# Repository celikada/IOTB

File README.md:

# IOTB
### Internet of Things Device
#### Version 3.0: 2021-1-17 [Wiki](https://github.com/celikada/IOTB/wiki)

#### Get expedited support or integration consultation for IOTB [from IOTECH](http://iotech.com.tr/)

---

### OVERVIEW:
IOTB is an internet of things edge device implementation. The hardware has digital inputs and outputs and offers connectivity for analog sensors and extensions.
It has open source firmware and upload ready various tcp/ip connection options according to needs.

**It is a platform**

IOTB is a platform that users can create and upload a firmware which they needed. 

**Main features:**
1. 100Mb Ethernet.
2. TTL Serial connection.
3. 8 Digital Inputs.
4. 8 Digital Outputs.
5. 5V-26V operational power range.
6. Opto isolation for IO.
7. 2 line (4+4) Isolated input voltage. 
8. Isolaated Output voltage.
9. Current protection for outputs.
10. Voltage progection for outputs.

STM32 architectute. Modbus and MQTT ready software.

### Changelog is located [here.](https://github.com/celikada/IOTB/wiki/Changelog)

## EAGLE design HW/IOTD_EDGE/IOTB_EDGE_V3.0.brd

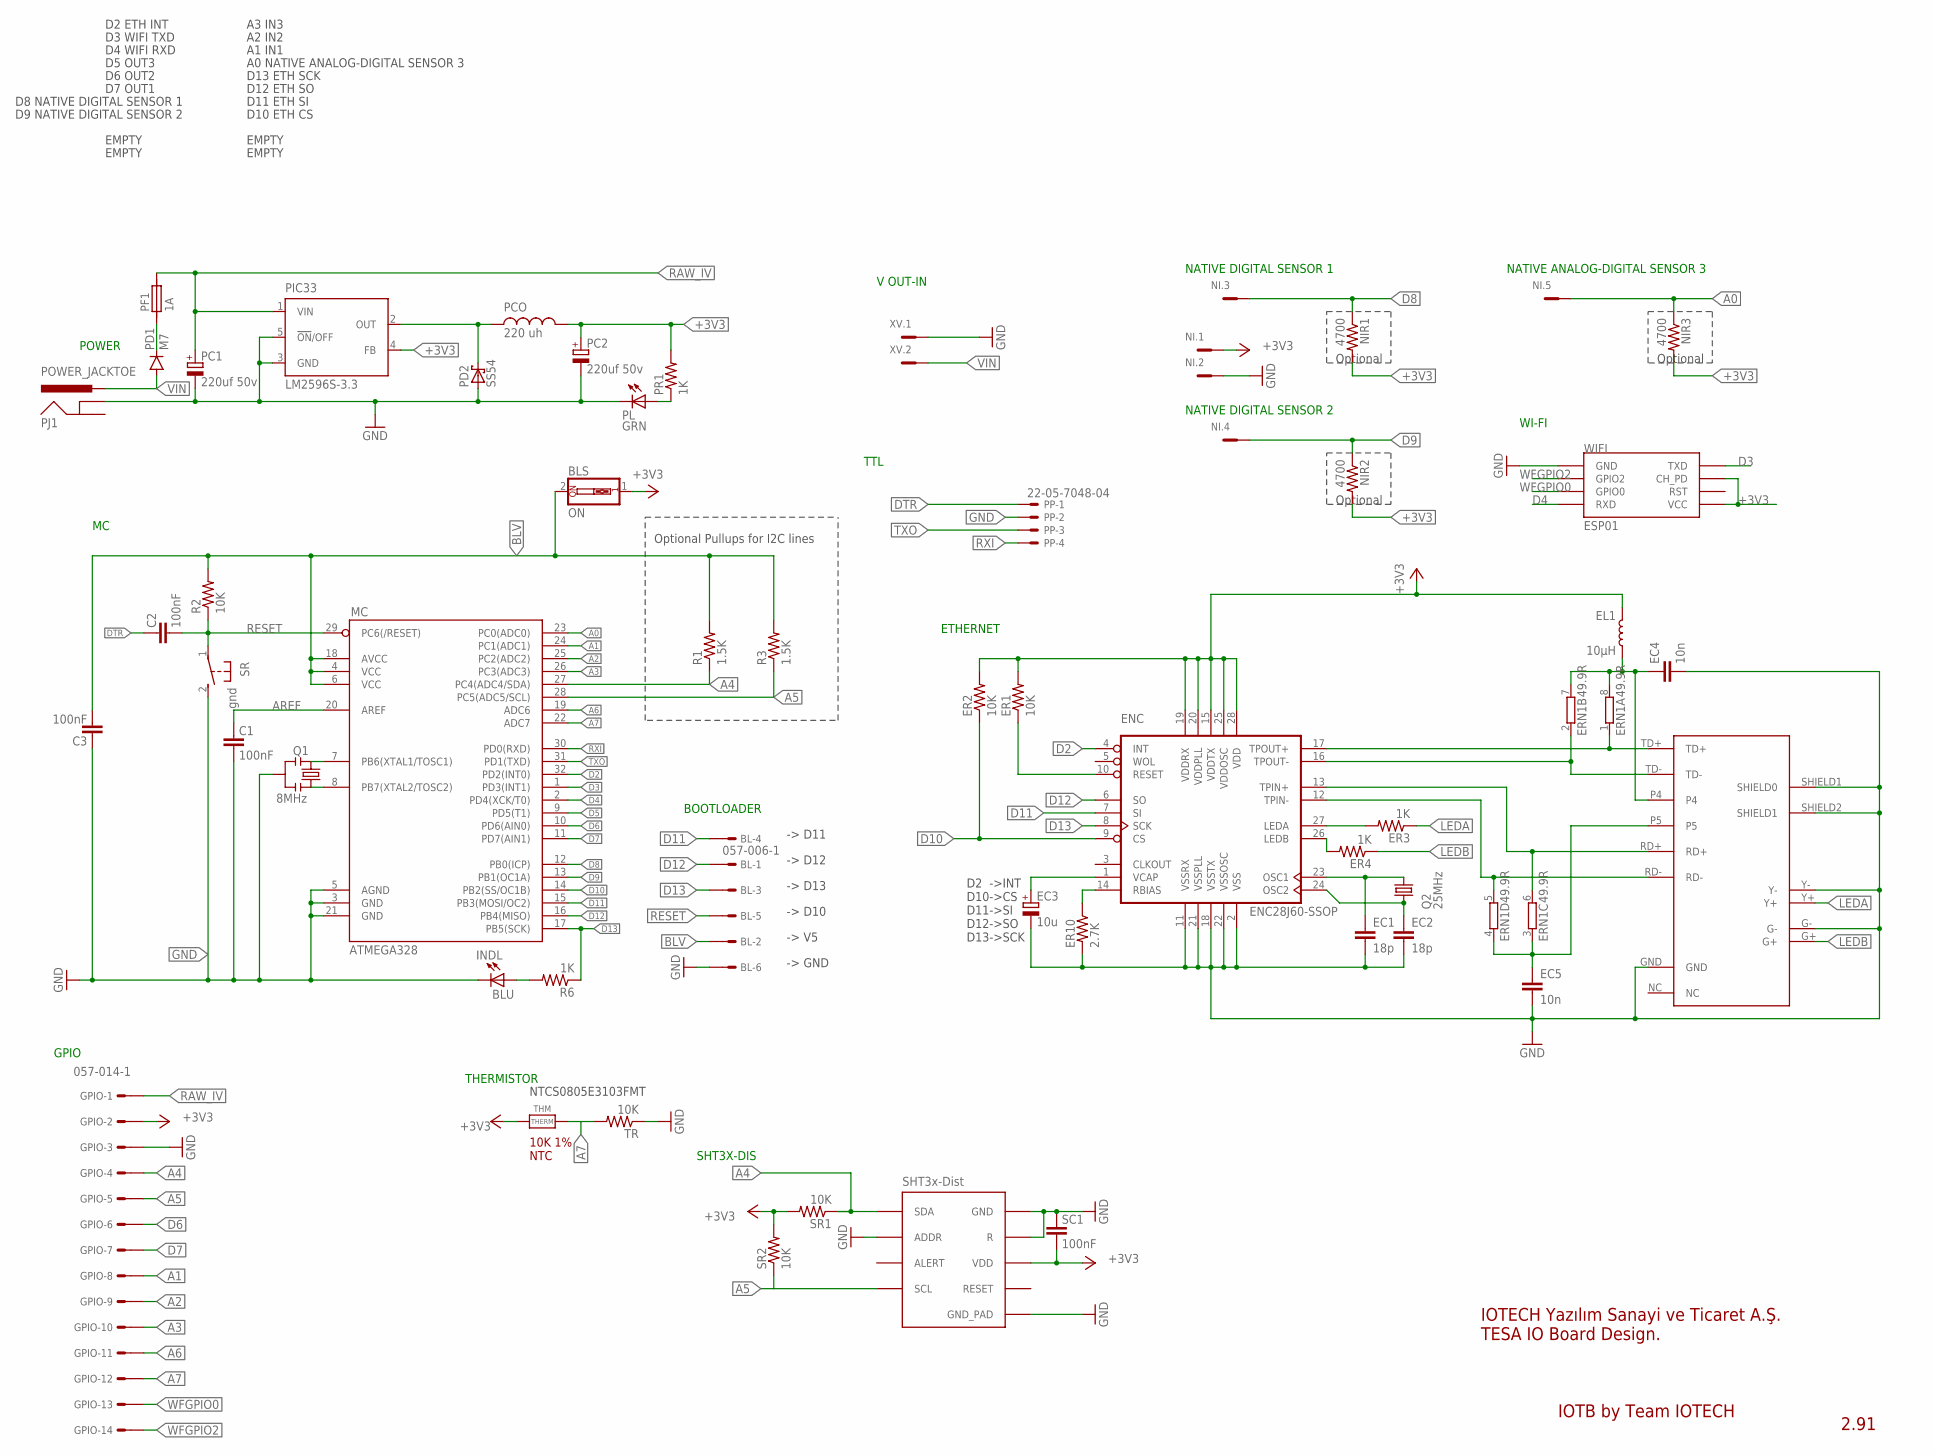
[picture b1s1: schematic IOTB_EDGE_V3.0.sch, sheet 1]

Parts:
BL: 057-006-1
BLS: ON; EDG-01
C1, C2, C3: 100nF; 0805
EC1, EC2: 18p; 0805
EC3: 10u; CT3216
EC4, EC5: 10n; 0805
EL1: 10µH; 0805
ENC: ENC28J60-SSOP; SSOP28
ER1, ER2: 10K; 0805
ER3, ER4: 1K; 0805
ER10: 2.7K; 0805
ERN1: 49.9R; 0603-ARV
ETHSOC: HR911105A; RJ45
GPIO: 057-014-1
INDL: BLU; CHIP-LED0805
MC: ATMEGA328; TQFP32-08
NI: MC5
NIR1, NIR2, NIR3: 4700; 0805
PC1, PC2: 220uf 50v; 140CLH-1010
PCO: 220 uh; MSS1260
PD1: M7; SMA-DIODE
PD2: SS54; SMB
PF1: 1A; 1820
PIC33: LM2596S-3.3; TO263-5
PJ1: POWER_JACKTOE; POWER_JACK_SMD_OVERPASTE_TOE
PL: GRN; CHIP-LED0805
PP: 22-05-7048-04; 7395-04
PR1: 1K; 0805
Q1: 8MHz; RESONATOR-SMD-1:1
Q2: 25MHz; 5.0X3.2_2
R1, R3: 1.5K; 0805
R2: 10K; 0805
R6: 1K; 0805
SC1: 100nF; 0805
SHT: SHT3X
SR: gnd; B3F-31XX
SR1, SR2: 10K; 0805
THM: THERM; MICROBUILDER_0805_NOTHERMALS
TR: 10K; 0805
WIFI: ESP01
XV: MC2

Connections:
+3V3: BLS.1, EL1.1, ENC.15 (VDDTX), ENC.19 (VDDRX), ENC.20 (VDDPLL), ENC.25 (VDDOSC), ENC.28 (VDD), ER1.2, ER2.2, GPIO.2, NI.1, NIR1.2, NIR2.2, NIR3.2, PC2.+, PCO.P$1, PIC33.4 (FB), PR1.2, SC1.1, SHT.VDD, SR1.2, SR2.2, THM.1, WIFI.CH_PD, WIFI.VCC; also elsewhere on the board
A0: MC.23 (PC0(ADC0)), NI.5, NIR3.1
A1: GPIO.8, MC.24 (PC1(ADC1))
A2: GPIO.9, MC.25 (PC2(ADC2))
A3: GPIO.10, MC.26 (PC3(ADC3))
A4: GPIO.4, MC.27 (PC4(ADC4/SDA)), R1.1, SHT.SDA, SR1.1; also elsewhere on the board
A5: GPIO.5, MC.28 (PC5(ADC5/SCL)), R3.1, SHT.SCL, SR2.1; also elsewhere on the board
A6: GPIO.11, MC.19 (ADC6)
A7: GPIO.12, MC.22 (ADC7), THM.2, TR.2
AREF: C1.2, MC.20 (AREF)
BLV: BL.2, BLS.2, C3.1, MC.4 (VCC), MC.6 (VCC), MC.18 (AVCC), R1.2, R2.2, R3.2
D2: ENC.4 (INT), MC.32 (PD2(INT0))
D3: MC.1 (PD3(INT1)), WIFI.TX (TXD)
D4: MC.2 (PD4(XCK/T0)), WIFI.RX (RXD)
D5: MC.9 (PD5(T1)); also elsewhere on the board
D6: GPIO.6, MC.10 (PD6(AIN0))
D7: GPIO.7, MC.11 (PD7(AIN1))
D8: MC.12 (PB0(ICP)), NI.3, NIR1.1
D9: MC.13 (PB1(OC1A)), NI.4, NIR2.1
D10: ENC.9 (CS), ER2.1, MC.14 (PB2(SS/OC1B))
D11: BL.4, ENC.7 (SI), MC.15 (PB3(MOSI/OC2))
D12: BL.1, ENC.6 (SO), MC.16 (PB4(MISO))
D13: BL.3, ENC.8 (SCK), MC.17 (PB5(SCK)), R6.1
DTR: C2.2, PP.1
EP4: EC4.1, EL1.2, ERN1.7 (2), ERN1.8 (2), ETHSOC.P4
EP5: EC5.1, ERN1.3 (1), ERN1.4 (1), ETHSOC.P5
GND: BL.6, C1.1, C3.2, EC1.2, EC2.2, EC3.-, EC4.2, EC5.2, ENC.2 (VSS), ENC.11 (VSSRX), ENC.18 (VSSTX), ENC.21 (VSSPLL), ENC.22 (VSSOSC), ER10.2, ETHSOC.G-, ETHSOC.GND, ETHSOC.SHIELD1 (SHIELD0), ETHSOC.SHIELD2 (SHIELD1), ETHSOC.Y-, GPIO.3, INDL.C, MC.3 (GND), MC.5 (AGND), MC.21 (GND), NI.2, PC1.-, PC2.-, PD2.A, PIC33.3 (GND), PIC33.5 (!ON!/OFF), PJ1.GND (GNDBREAK), PL.C, PP.2, Q1.2, SC1.2, SHT.ADDR, SHT.GND, SHT.GND_PAD, SHT.R, SR.2 (S), TR.1, WIFI.GND, XV.1; also elsewhere on the board
LEDA: ER3.1, ETHSOC.Y+
LEDB: ER4.1, ETHSOC.G+
unnamed: PD1.C, PF1.1
unnamed: INDL.A, R6.2
unnamed: ENC.27 (LEDA), ER3.2
unnamed: MC.8 (PB7(XTAL2/TOSC2)), Q1.3
unnamed: PL.A, PR1.1
unnamed: EC3.+, ENC.1 (VCAP)
unnamed: ENC.26 (LEDB), ER4.2
unnamed: MC.7 (PB6(XTAL1/TOSC1)), Q1.1
unnamed: PCO.P$2, PD2.C, PIC33.2 (OUT)
unnamed: ENC.10 (RESET), ER1.1
unnamed: ENC.14 (RBIAS), ER10.1
unnamed: EC2.1, ENC.24 (OSC2), Q2.1
unnamed: EC1.1, ENC.23 (OSC1), Q2.2
RAW_IV: GPIO.1, PC1.+, PF1.2, PIC33.1 (VIN)
RD+: ENC.13 (TPIN+), ERN1.6 (2), ETHSOC.RD+
RD-: ENC.12 (TPIN-), ERN1.5 (2), ETHSOC.RD-
RESET: BL.5, C2.1, MC.29 (PC6(/RESET)), R2.1, SR.1
RXI: MC.30 (PD0(RXD)), PP.4
TD+: ENC.17 (TPOUT+), ERN1.1, ETHSOC.TD+
TD-: ENC.16 (TPOUT-), ERN1.2 (1), ETHSOC.TD-
TXO: MC.31 (PD1(TXD)), PP.3
VIN: PD1.A, PJ1.VIN0 (PWR), XV.2
WFGPIO0: GPIO.13, WIFI.GPIO0
WFGPIO2: GPIO.14, WIFI.GPIO2

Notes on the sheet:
POWER
NATIVE DIGITAL SENSOR 1
NATIVE DIGITAL SENSOR 2
WI-FI
NATIVE ANALOG-DIGITAL SENSOR 3
IOTB by Team IOTECH
2.91
ETHERNET
D2 ->INT D10->CS D11->SI D12->SO D13->SCK
TTL
IOTECH Yazılım Sanayi ve Ticaret A.Ş. TESA IO Board Design.
Optional Pullups for I2C lines
D2 ETH INT
D8 NATIVE DIGITAL SENSOR 1
D9 NATIVE DIGITAL SENSOR 2
EMPTY
A3 IN3
A2 IN2
A1 IN1
A0 NATIVE ANALOG-DIGITAL SENSOR 3
D13 ETH SCK
D12 ETH SO
D11 ETH SI
D10 ETH CS
D4 WIFI RXD
D3 WIFI TXD
D7 OUT1
D6 OUT2
D5 OUT3
BOOTLOADER
-> D11
-> D12
-> D13
-> D10
-> V5
-> GND
Optional
V OUT-IN
GPIO
NTCS0805E3103FMT

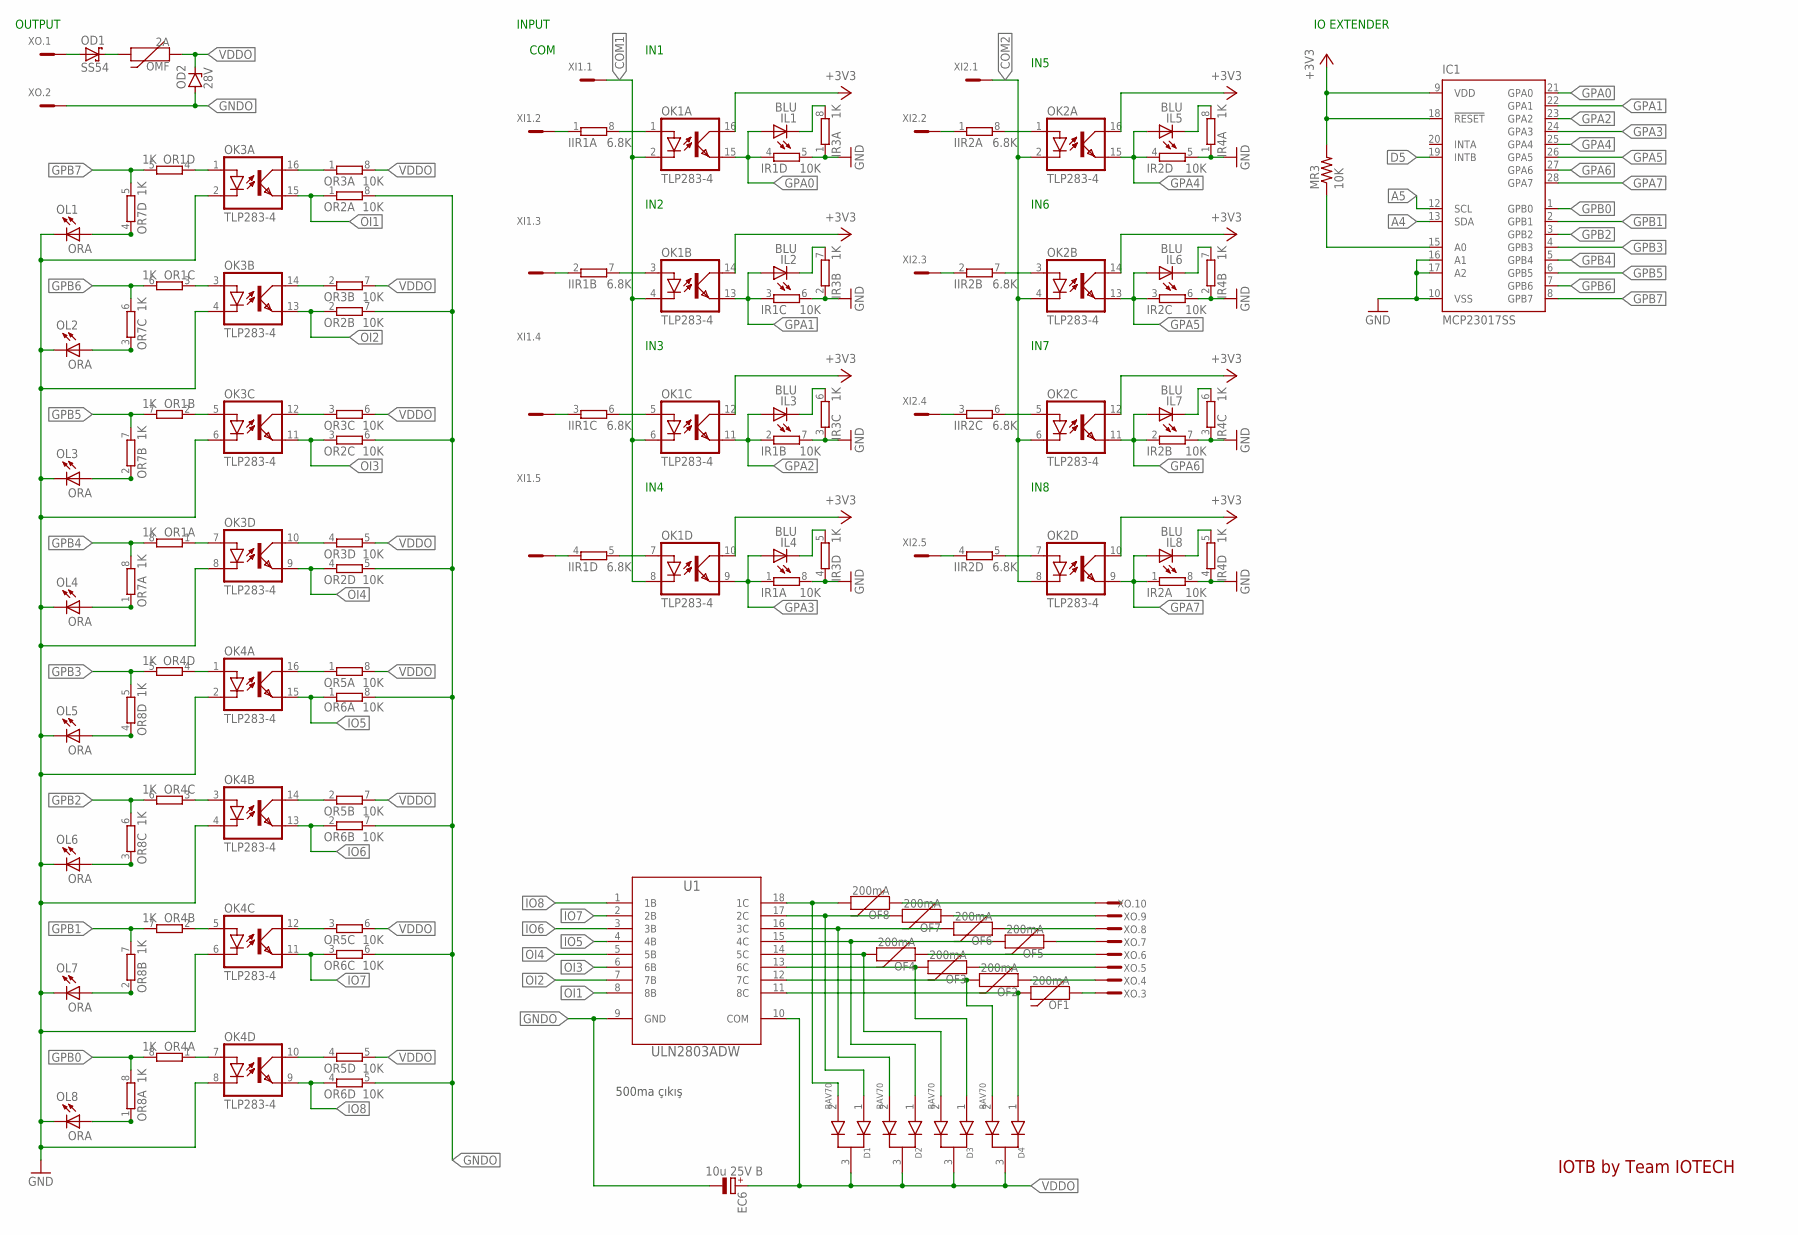
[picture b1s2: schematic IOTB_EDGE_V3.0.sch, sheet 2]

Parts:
D1, D2, D3, D4: BAV70; SOT-23-3
EC6: 10u 25V B; SMC_B
IC1: MCP23017SS; SSOP28
IIR1, IIR2: 6.8K; 0603-ARV
IL1, IL2, IL3, IL4, IL5, IL6, IL7, IL8: BLU; CHIP-LED0805
IR1, IR2: 10K; 0603-ARV
IR3, IR4: 1K; 0603-ARV
MR3: 10K; 0805
OD1: SS54; SMB
OD2: 28V; SMB
OF1, OF2, OF3, OF4, OF5, OF6, OF7, OF8: 200mA; 1206
OK1, OK2, OK3, OK4: TLP283-4; MINI-FLAT-16
OL1, OL2, OL3, OL4, OL5, OL6, OL7, OL8: ORA; CHIP-LED0805
OMF: 2A; 1206
OR1, OR4, OR7, OR8: 1K; 0603-ARV
OR2, OR3, OR5, OR6: 10K; 0603-ARV
U1: ULN2803ADW; SOIC127P1030X265-18N
XI1, XI2: MC5
XO: MC10

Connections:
+3V3: IC1.9 (VDD), IC1.18 (!RESET), MR3.2, OK1.10 (COL), OK1.12 (COL), OK1.14 (COL), OK1.16 (COL), OK2.10 (COL), OK2.12 (COL), OK2.14 (COL), OK2.16 (COL); also elsewhere on the board
A4: IC1.13 (SDA); also elsewhere on the board
A5: IC1.12 (SCL); also elsewhere on the board
COM1: OK1.2 (C), OK1.4 (C), OK1.6 (C), OK1.8 (C), XI1.1
COM2: OK2.2 (C), OK2.4 (C), OK2.6 (C), OK2.8 (C), XI2.1
D5: IC1.19 (INTB); also elsewhere on the board
GND: IC1.10 (VSS), IC1.16 (A1), IC1.17 (A2), IR1.5 (2), IR1.6 (2), IR1.7 (2), IR1.8 (2), IR2.5 (2), IR2.6 (2), IR2.7 (2), IR2.8 (2), IR3.1, IR3.2 (1), IR3.3 (1), IR3.4 (1), IR4.1, IR4.2 (1), IR4.3 (1), IR4.4 (1), OK3.2 (C), OK3.4 (C), OK3.6 (C), OK3.8 (C), OK4.2 (C), OK4.4 (C), OK4.6 (C), OK4.8 (C), OL1.C, OL2.C, OL3.C, OL4.C, OL5.C, OL6.C, OL7.C, OL8.C; also elsewhere on the board
GNDO: EC6.-, OD2.A, OR2.5 (2), OR2.6 (2), OR2.7 (2), OR2.8 (2), OR6.5 (2), OR6.6 (2), OR6.7 (2), OR6.8 (2), U1.9 (GND), XO.2
GPA0: IC1.21 (GPA0), IL1.A, IR1.4 (1), OK1.15 (EMIT)
GPA1: IC1.22 (GPA1), IL2.A, IR1.3 (1), OK1.13 (EMIT)
GPA2: IC1.23 (GPA2), IL3.A, IR1.2 (1), OK1.11 (EMIT)
GPA3: IC1.24 (GPA3), IL4.A, IR1.1, OK1.9 (EMIT)
GPA4: IC1.25 (GPA4), IL5.A, IR2.4 (1), OK2.15 (EMIT)
GPA5: IC1.26 (GPA5), IL6.A, IR2.3 (1), OK2.13 (EMIT)
GPA6: IC1.27 (GPA6), IL7.A, IR2.2 (1), OK2.11 (EMIT)
GPA7: IC1.28 (GPA7), IL8.A, IR2.1, OK2.9 (EMIT)
GPB0: IC1.1 (GPB0), OR4.8 (2), OR8.8 (2)
GPB1: IC1.2 (GPB1), OR4.7 (2), OR8.7 (2)
GPB2: IC1.3 (GPB2), OR4.6 (2), OR8.6 (2)
GPB3: IC1.4 (GPB3), OR4.5 (2), OR8.5 (2)
GPB4: IC1.5 (GPB4), OR1.8 (2), OR7.8 (2)
GPB5: IC1.6 (GPB5), OR1.7 (2), OR7.7 (2)
GPB6: IC1.7 (GPB6), OR1.6 (2), OR7.6 (2)
GPB7: IC1.8 (GPB7), OR1.5 (2), OR7.5 (2)
IO5: OK4.15 (EMIT), OR6.1, U1.4 (4B)
IO6: OK4.13 (EMIT), OR6.2 (1), U1.3 (3B)
IO7: OK4.11 (EMIT), OR6.3 (1), U1.2 (2B)
IO8: OK4.9 (EMIT), OR6.4 (1), U1.1 (1B)
unnamed: OD1.A, XO.1
unnamed: IC1.15 (A0), MR3.1
unnamed: OD1.C, OMF.2
unnamed: OF8.1, XO.10
unnamed: D1.1, OF7.2, U1.17 (2C)
unnamed: OK3.1 (A), OR1.4 (1)
unnamed: IL1.C, IR3.8 (2)
unnamed: IIR1.1, XI1.2
unnamed: IL2.C, IR3.7 (2)
unnamed: IL3.C, IR3.6 (2)
unnamed: IL4.C, IR3.5 (2)
unnamed: IL5.C, IR4.8 (2)
unnamed: IL6.C, IR4.7 (2)
unnamed: IL7.C, IR4.6 (2)
unnamed: IIR1.2 (1), XI1.3
unnamed: IIR1.8 (2), OK1.1 (A)
unnamed: IIR1.7 (2), OK1.3 (A)
unnamed: IIR1.6 (2), OK1.5 (A)
unnamed: IIR1.5 (2), OK1.7 (A)
unnamed: IIR1.3 (1), XI1.4
unnamed: IIR1.4 (1), XI1.5
unnamed: OK3.3 (A), OR1.3 (1)
unnamed: IIR2.1, XI2.2
unnamed: IIR2.8 (2), OK2.1 (A)
unnamed: IIR2.2 (1), XI2.3
unnamed: IIR2.7 (2), OK2.3 (A)
unnamed: IIR2.3 (1), XI2.4
unnamed: IIR2.6 (2), OK2.5 (A)
unnamed: IIR2.4 (1), XI2.5
unnamed: IIR2.5 (2), OK2.7 (A)
unnamed: IL8.C, IR4.5 (2)
unnamed: OK3.5 (A), OR1.2 (1)
unnamed: OK3.7 (A), OR1.1
unnamed: D1.2, OF8.2, U1.18 (1C)
unnamed: OK3.16 (COL), OR3.1
unnamed: D2.2, OF6.2, U1.16 (3C)
unnamed: D2.1, OF5.2, U1.15 (4C)
unnamed: OF7.1, XO.9
unnamed: OF6.1, XO.8
unnamed: OK3.14 (COL), OR3.2 (1)
unnamed: OF5.1, XO.7
unnamed: OF4.1, XO.6
unnamed: OK3.12 (COL), OR3.3 (1)
unnamed: D3.1, OF3.2, U1.13 (6C)
unnamed: OK3.10 (COL), OR3.4 (1)
unnamed: D4.2, OF2.2, U1.12 (7C)
unnamed: OL1.A, OR7.4 (1)
unnamed: OL2.A, OR7.3 (1)
unnamed: OL3.A, OR7.2 (1)
unnamed: OL4.A, OR7.1
unnamed: D4.1, OF1.2, U1.11 (8C)
unnamed: D3.2, OF4.2, U1.14 (5C)
unnamed: OF3.1, XO.5
unnamed: OF2.1, XO.4
unnamed: OF1.1, XO.3
unnamed: OK4.1 (A), OR4.4 (1)
unnamed: OK4.3 (A), OR4.3 (1)
unnamed: OK4.5 (A), OR4.2 (1)
unnamed: OK4.7 (A), OR4.1
unnamed: OK4.16 (COL), OR5.1
unnamed: OK4.14 (COL), OR5.2 (1)
unnamed: OK4.12 (COL), OR5.3 (1)
unnamed: OK4.10 (COL), OR5.4 (1)
unnamed: OL5.A, OR8.4 (1)
unnamed: OL6.A, OR8.3 (1)
unnamed: OL7.A, OR8.2 (1)
unnamed: OL8.A, OR8.1
OI1: OK3.15 (EMIT), OR2.1, U1.8 (8B)
OI2: OK3.13 (EMIT), OR2.2 (1), U1.7 (7B)
OI3: OK3.11 (EMIT), OR2.3 (1), U1.6 (6B)
OI4: OK3.9 (EMIT), OR2.4 (1), U1.5 (5B)
VDDO: D1.3, D2.3, D3.3, D4.3, EC6.+, OD2.C, OMF.1, OR3.5 (2), OR3.6 (2), OR3.7 (2), OR3.8 (2), OR5.5 (2), OR5.6 (2), OR5.7 (2), OR5.8 (2), U1.10 (COM)

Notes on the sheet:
IOTB by Team IOTECH
INPUT
IN1
IN2
IN3
IN4
IN5
IN6
IN7
IN8
COM
OUTPUT
IO EXTENDER
500ma çıkış

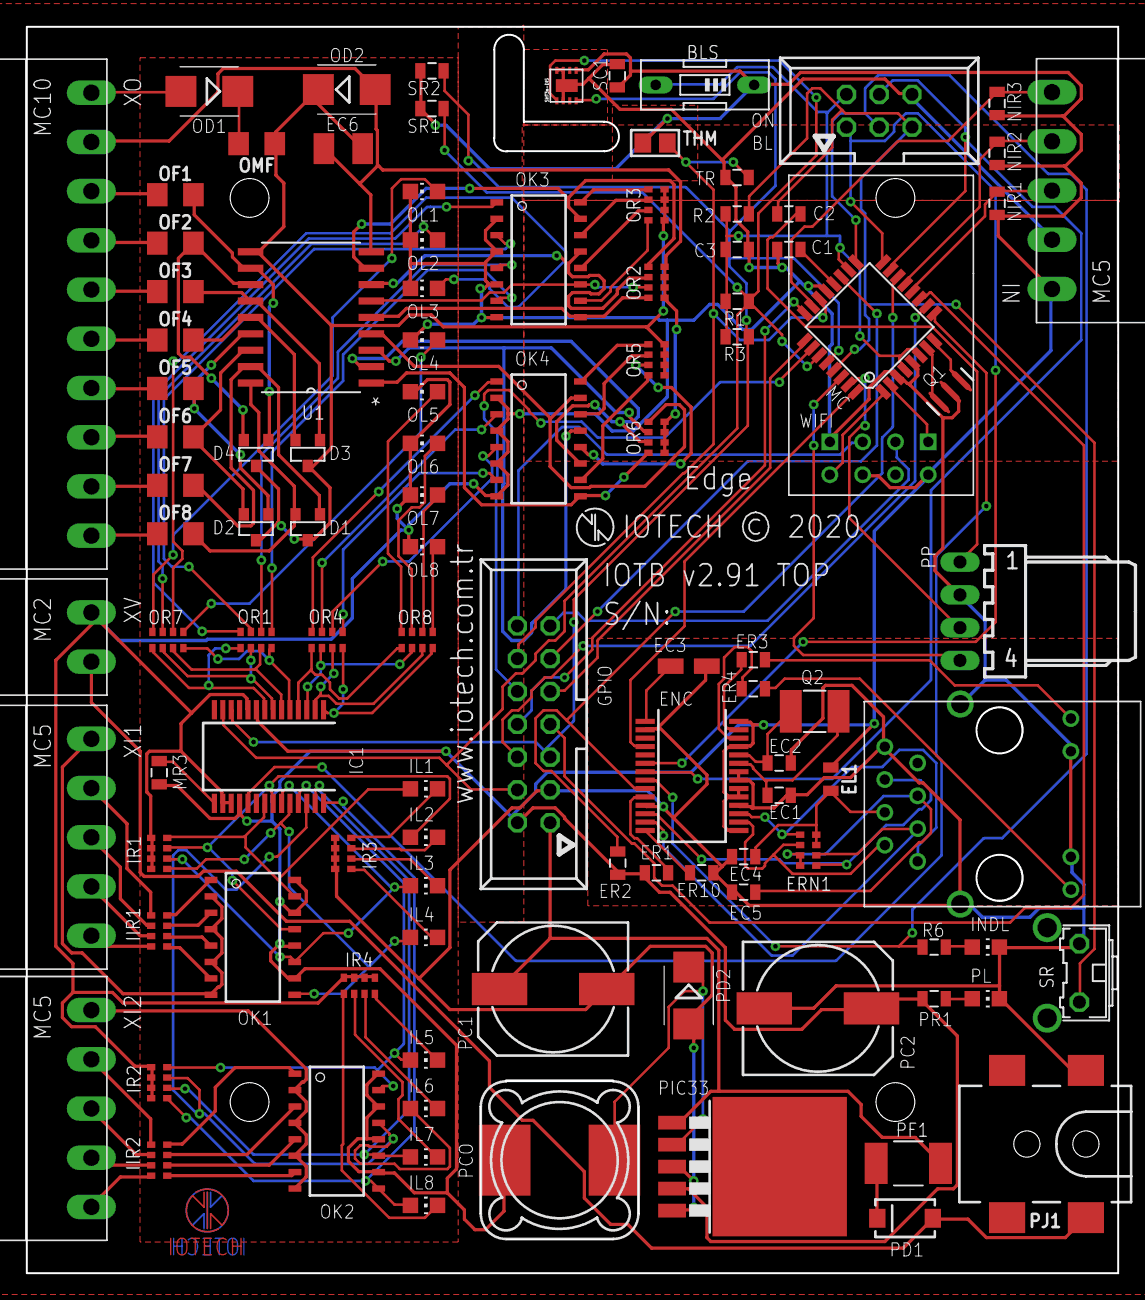
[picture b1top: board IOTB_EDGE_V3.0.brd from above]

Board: 2 copper layers, 84.5 x 96.5 mm, 110 parts (1 on the bottom side), 148 nets.

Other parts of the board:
LOGOB: IOTECH_COPPER_W_TEXT
LOGOT: IOTECH_COPPER_W_TEXT

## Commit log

2021-01-17 init commit
2021-01-17 watchdog
2021-03-01 kes pro init
2021-03-02 esp serial comm test
2021-03-03 send countdown add
2021-03-07 drop water

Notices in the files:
HW/IOTD_EDGE/IOTB_EDGE_V3.0.brd:
IOTECH © 2020
parts and their libraries:
SparkFun-DiscreteSemi: Licensing: Creative Commons ShareAlike 4.0 International - https://creativecommons.org/licenses/by-sa/4.0
crystal-geyer_V1_0: Copyright: Geyer-Electronic
